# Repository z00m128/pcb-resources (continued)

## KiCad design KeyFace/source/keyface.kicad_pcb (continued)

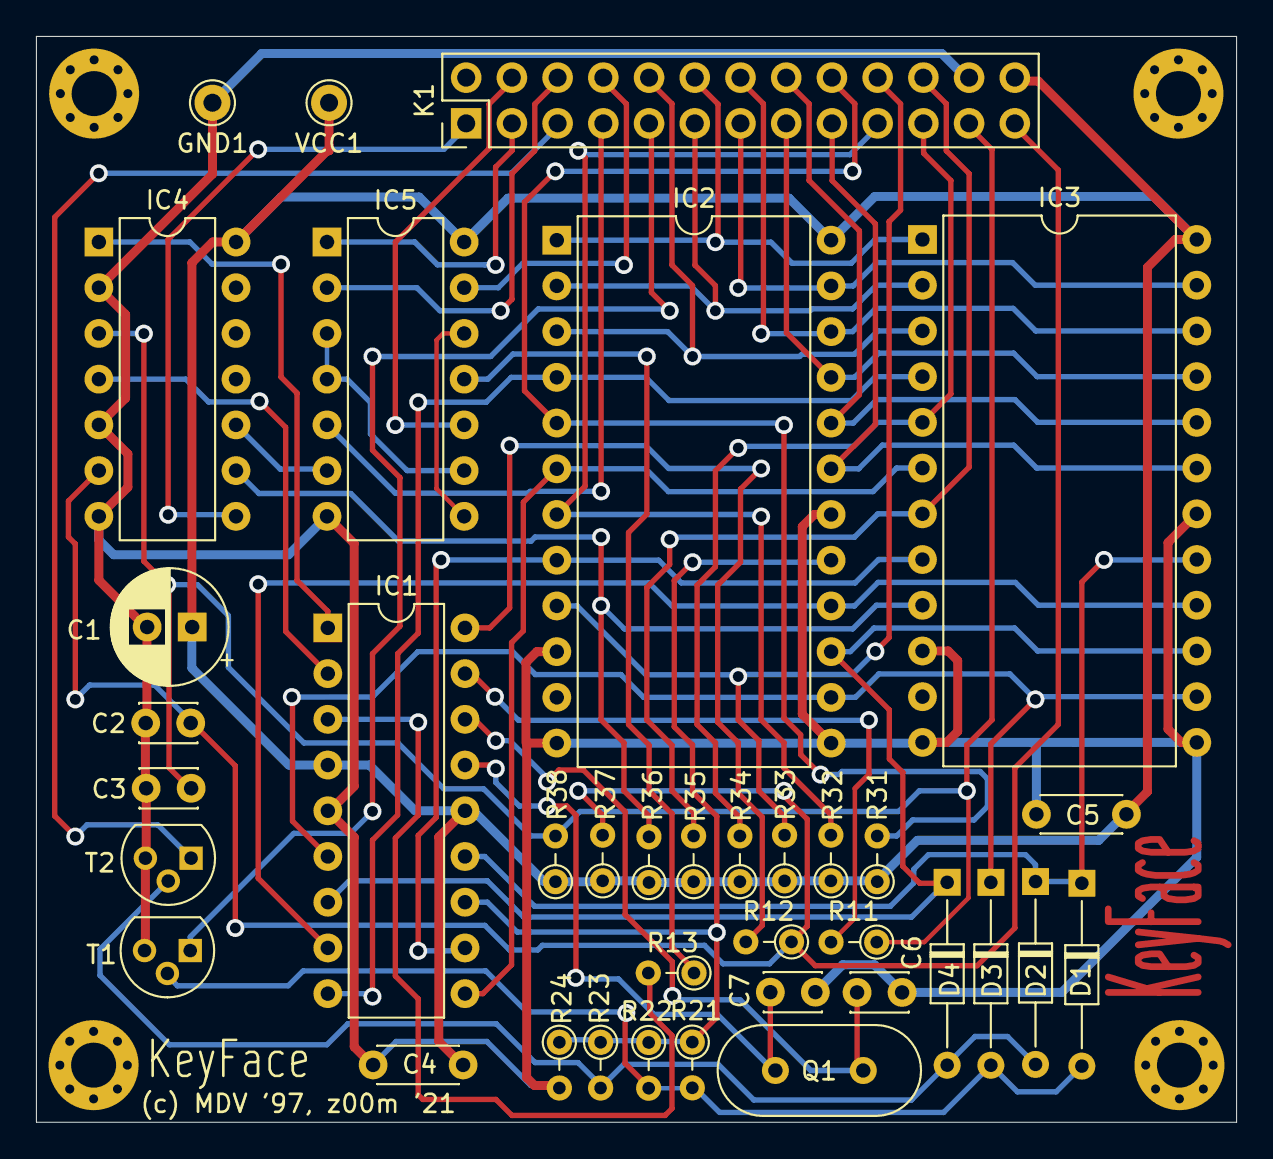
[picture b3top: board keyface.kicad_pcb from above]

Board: 2 copper layers, 66.7 x 60.3 mm, 41 parts (0 on the bottom side), 47 nets.

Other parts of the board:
H1, H2, H3, H4: MountingHole_2.5mm_Pad_Via

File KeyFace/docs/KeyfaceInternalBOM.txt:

C1               1  100uF                 Polarized capacitor, radial, 6.3mm x 2.5mm
C2,C3            2  47p                   Unpolarized capacitor, disc, 3 mm x 2mm x 2.5mm
C4,C5            2  100n                  Unpolarized capacitor, disc, 4.3 mm x 1.9mm x 5mm
C6,C7            2  33p                   Unpolarized capacitor, disc, 3 mm x 2mm x 2.5mm
D1,D2,D3,D4      4  BAT42                 Diode schottky, DO-35
IC1              1  PIC16C56 or PIC16F84  Micro controller, DIP 18
IC2,IC3          2  MHB8804               Analog switching array, DIP 24W
IC4              1  74HCT125              Quad buffer 3-State outputs, DIP 14
IC5              1  74HCT32               Quad 2-input OR, DIP 14
Q1               1  4 MHz                 Two pin crystal, HC49U (H49S), THT
R11,R12,R13      3  560R                  Resistor 0.25W, small, THT
R21,R22,R23,R24  4  10k                   Resistor 0.25W, small, THT
R31,R32,R33,R34  8  4k7                   Resistor 0.25W, small, THT
R35,R36,R37,R38  
T1,T2            1  BC547                 0.1A Ic, 45V Vce, Small Signal NPN Transistor, TO-92
K1               1  Conn_02x13_Odd_Even   Generic connector, double row, 2x13, 2.54 mm raster

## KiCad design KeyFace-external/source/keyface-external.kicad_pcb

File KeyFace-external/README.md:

# KeyFace External for ZX Spectrum
A PS/2 keyboard interface for ZX Spectrum, external version. This PCB was created from scratch, but I tried to mimic component layout as was seen on original PCB from Kompakt Servis. It's verified and working.

## Schematic Diagram

## Populated PCB

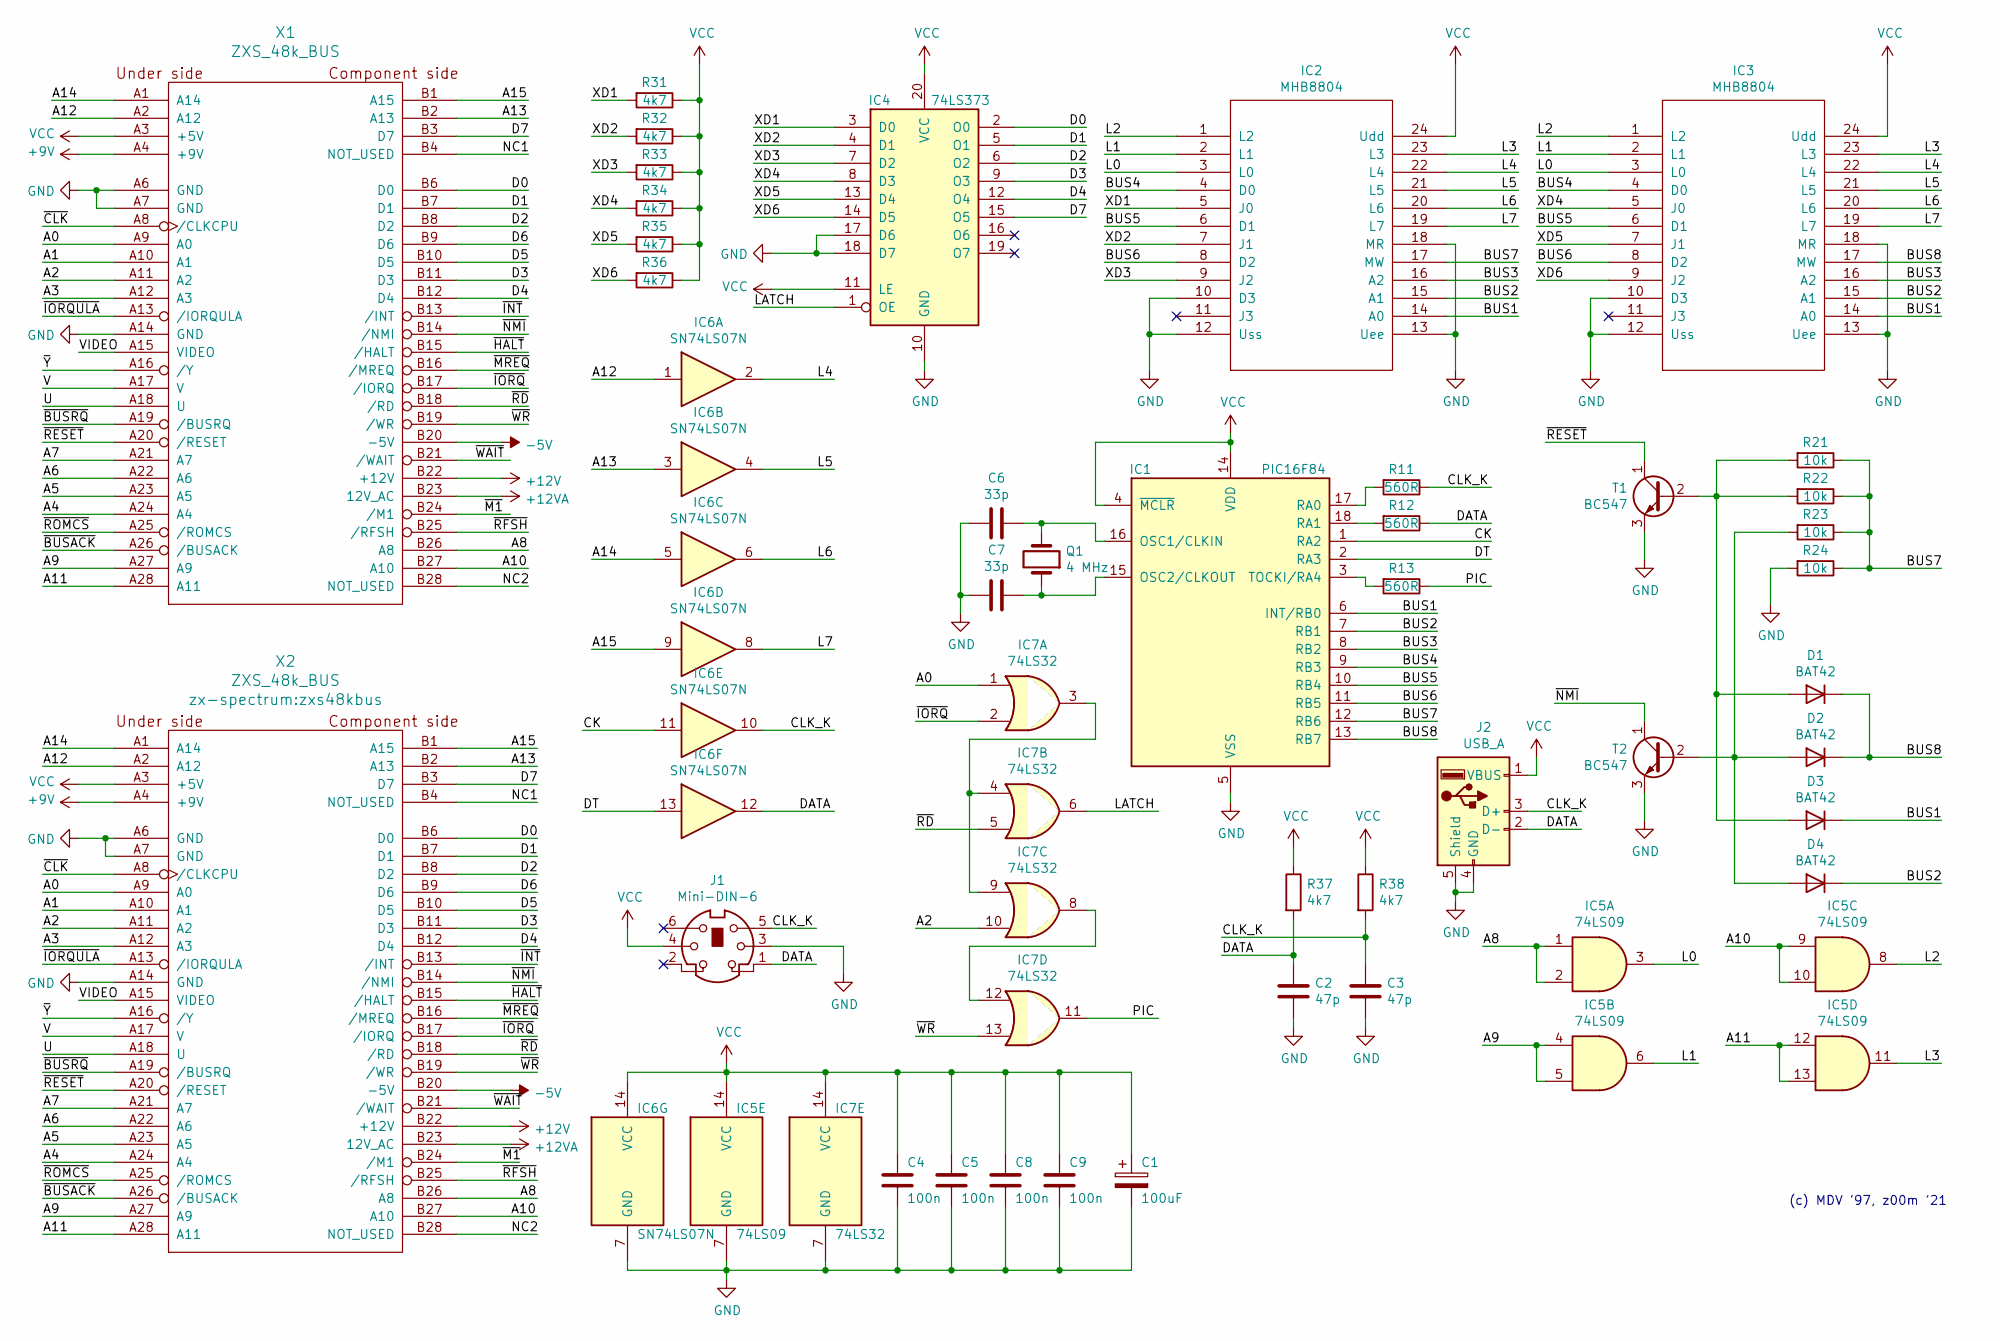
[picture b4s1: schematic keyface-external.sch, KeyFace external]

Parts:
C1: 100uF; CP_Radial_D6.3mm_P2.50mm
C2, C3: 47p; C_Disc_D3.0mm_W2.0mm_P2.50mm
C4, C5, C8, C9: 100n; C_Disc_D4.3mm_W1.9mm_P5.00mm
C6, C7: 33p; C_Disc_D3.0mm_W2.0mm_P2.50mm
D1, D2, D3, D4: BAT42; D_DO-35_SOD27_P7.62mm_Horizontal
IC1: PIC16F84; DIP-18_W7.62mm
IC2, IC3: MHB8804; DIP-24_W15.24mm
IC4: 74LS373; DIP-20_W7.62mm
IC5: 74LS09; DIP-14_W7.62mm
IC6: SN74LS07N; DIP-14_W7.62mm
IC7: 74LS32; DIP-14_W7.62mm
J1: Mini-DIN-6; MiniDin6
J2: USB_A; USB_A_Wuerth_614004134726_Horizontal
Q1: 4 MHz; Crystal_HC49-U_Vertical
R11, R12, R13: 560R; R_Axial_DIN0204_L3.6mm_D1.6mm_P2.54mm_Vertical
R21, R22, R23, R24: 10k; R_Axial_DIN0204_L3.6mm_D1.6mm_P2.54mm_Vertical
R31, R32, R33, R34, R35, R36, R37, R38: 4k7; R_Axial_DIN0204_L3.6mm_D1.6mm_P2.54mm_Vertical
T1, T2: BC547; TO-92
X1, X2: ZXS_48k_BUS; zxs48kbus

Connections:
+9V: X1.A4 (+9V), X2.A4 (+9V)
+12V: X1.B22 (+12V), X2.B22 (+12V)
+12VA: X1.B23 (12V_AC), X2.B23 (12V_AC)
-5V: X1.B20 (-5V), X2.B20 (-5V)
/A0: IC7.1, X1.A9 (A0), X2.A9 (A0)
/A1: X1.A10 (A1), X2.A10 (A1)
/A2: IC7.10, X1.A11 (A2), X2.A11 (A2)
/A3: X1.A12 (A3), X2.A12 (A3)
/A4: X1.A24 (A4), X2.A24 (A4)
/A5: X1.A23 (A5), X2.A23 (A5)
/A6: X1.A22 (A6), X2.A22 (A6)
/A7: X1.A21 (A7), X2.A21 (A7)
/A8: IC5.1, IC5.2, X1.B26 (A8), X2.B26 (A8)
/A9: IC5.4, IC5.5, X1.A27 (A9), X2.A27 (A9)
/A10: IC5.9, IC5.10, X1.B27 (A10), X2.B27 (A10)
/A11: IC5.12, IC5.13, X1.A28 (A11), X2.A28 (A11)
/A12: IC6.1, X1.A2 (A12), X2.A2 (A12)
/A13: IC6.3, X1.B2 (A13), X2.B2 (A13)
/A14: IC6.5, X1.A1 (A14), X2.A1 (A14)
/A15: IC6.9, X1.B1 (A15), X2.B1 (A15)
/BUS1: D3.1 (K), IC1.6 (INT/RB0), IC2.14 (A0), IC3.14 (A0)
/BUS2: D4.1 (K), IC1.7 (RB1), IC2.15 (A1), IC3.15 (A1)
/BUS3: IC1.8 (RB2), IC2.16 (A2), IC3.16 (A2)
/BUS4: IC1.9 (RB3), IC2.4 (D0), IC3.4 (D0)
/BUS5: IC1.10 (RB4), IC2.6 (D1), IC3.6 (D1)
/BUS6: IC1.11 (RB5), IC2.8 (D2), IC3.8 (D2)
/BUS7: IC1.12 (RB6), IC2.17 (MW), R21.1, R22.1, R23.1, R24.1
/BUS8: D1.1 (K), D2.1 (K), IC1.13 (RB7), IC3.17 (MW)
/CK: IC1.1 (RA2), IC6.11
/CLK_K: C3.1, IC6.10, J1.5, J2.3 (D+), R11.1, R38.2
/D0: IC4.2 (O0), X1.B6 (D0), X2.B6 (D0)
/D1: IC4.5 (O1), X1.B7 (D1), X2.B7 (D1)
/D2: IC4.6 (O2), X1.B8 (D2), X2.B8 (D2)
/D3: IC4.9 (O3), X1.B11 (D3), X2.B11 (D3)
/D4: IC4.12 (O4), X1.B12 (D4), X2.B12 (D4)
/D5: X1.B10 (D5), X2.B10 (D5)
/D6: X1.B9 (D6), X2.B9 (D6)
/D7: IC4.15 (O5), X1.B3 (D7), X2.B3 (D7)
/DATA: C2.1, IC6.12, J1.1, J2.2 (D-), R12.1, R37.2
/DT: IC1.2 (RA3), IC6.13
/L0: IC2.3 (L0), IC3.3 (L0), IC5.3
/L1: IC2.2 (L1), IC3.2 (L1), IC5.6
/L2: IC2.1 (L2), IC3.1 (L2), IC5.8
/L3: IC2.23 (L3), IC3.23 (L3), IC5.11
/L4: IC2.22 (L4), IC3.22 (L4), IC6.2
/L5: IC2.21 (L5), IC3.21 (L5), IC6.4
/L6: IC2.20 (L6), IC3.20 (L6), IC6.6
/L7: IC2.19 (L7), IC3.19 (L7), IC6.8
/LATCH: IC4.1 (OE), IC7.6
/NC1: X1.B4 (NOT_USED), X2.B4 (NOT_USED)
/NC2: X1.B28 (NOT_USED), X2.B28 (NOT_USED)
/PIC: IC7.11, R13.1
/U: X1.A18 (U), X2.A18 (U)
/V: X1.A17 (V), X2.A17 (V)
/VIDEO: X1.A15 (VIDEO), X2.A15 (VIDEO)
/XD1: IC2.5 (J0), IC4.3 (D0), R31.2
/XD2: IC2.7 (J1), IC4.4 (D1), R32.2
/XD3: IC2.9 (J2), IC4.7 (D2), R33.2
/XD4: IC3.5 (J0), IC4.8 (D3), R34.2
/XD5: IC3.7 (J1), IC4.13 (D4), R35.2
/XD6: IC3.9 (J2), IC4.14 (D5), R36.2
/~BUSACK: X1.A26 (/BUSACK), X2.A26 (/BUSACK)
/~BUSRQ: X1.A19 (/BUSRQ), X2.A19 (/BUSRQ)
/~CLK: X1.A8 (/CLKCPU), X2.A8 (/CLKCPU)
/~HALT: X1.B15 (/HALT), X2.B15 (/HALT)
/~INT: X1.B13 (/INT), X2.B13 (/INT)
/~IORQ: IC7.2, X1.B17 (/IORQ), X2.B17 (/IORQ)
/~IORQULA: X1.A13 (/IORQULA), X2.A13 (/IORQULA)
/~M1: X1.B24 (/M1), X2.B24 (/M1)
/~MREQ: X1.B16 (/MREQ), X2.B16 (/MREQ)
/~NMI: T2.1 (C), X1.B14 (/NMI), X2.B14 (/NMI)
/~RD: IC7.5, X1.B18 (/RD), X2.B18 (/RD)
/~RESET: T1.1 (C), X1.A20 (/RESET), X2.A20 (/RESET)
/~RFSH: X1.B25 (/RFSH), X2.B25 (/RFSH)
/~ROMCS: X1.A25 (/ROMCS), X2.A25 (/ROMCS)
/~WAIT: X1.B21 (/WAIT), X2.B21 (/WAIT)
/~WR: IC7.13, X1.B19 (/WR), X2.B19 (/WR)
/~Y: X1.A16 (/Y), X2.A16 (/Y)
GND: C1.2, C2.2, C3.2, C4.2, C5.2, C6.2, C7.2, C8.2, C9.2, IC1.5 (VSS), IC2.10 (D3), IC2.12 (Uss), IC2.13 (Uee), IC2.18 (MR), IC3.10 (D3), IC3.12 (Uss), IC3.13 (Uee), IC3.18 (MR), IC4.10 (GND), IC4.17 (D6), IC4.18 (D7), IC5.7 (GND), IC6.7 (GND), IC7.7 (GND), J1.3, J2.4 (GND), J2.5 (Shield), R24.2, T1.3 (E), T2.3 (E), X1.A6 (GND), X1.A7 (GND), X1.A14 (GND), X2.A6 (GND), X2.A7 (GND), X2.A14 (GND)
unnamed: C6.1, IC1.16 (OSC1/CLKIN), Q1.2
unnamed: C7.1, IC1.15 (OSC2/CLKOUT), Q1.1
unnamed: D1.2 (A), D3.2 (A), R21.2, R22.2, T1.2 (B)
unnamed: D2.2 (A), D4.2 (A), R23.2, T2.2 (B)
unnamed: IC1.3 (TOCKI/RA4), R13.2
unnamed: IC1.17 (RA0), R11.2
unnamed: IC1.18 (RA1), R12.2
unnamed: IC7.3, IC7.4, IC7.9
unnamed: IC7.8, IC7.12
VCC: C1.1, C4.1, C5.1, C8.1, C9.1, IC1.4 (~MCLR~), IC1.14 (VDD), IC2.24 (Udd), IC3.24 (Udd), IC4.11 (LE), IC4.20 (VCC), IC5.14 (VCC), IC6.14 (VCC), IC7.14 (VCC), J1.4, J2.1 (VBUS), R31.1, R32.1, R33.1, R34.1, R35.1, R36.1, R37.1, R38.1, X1.A3 (+5V), X2.A3 (+5V)

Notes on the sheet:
(c) MDV '97, z00m '21

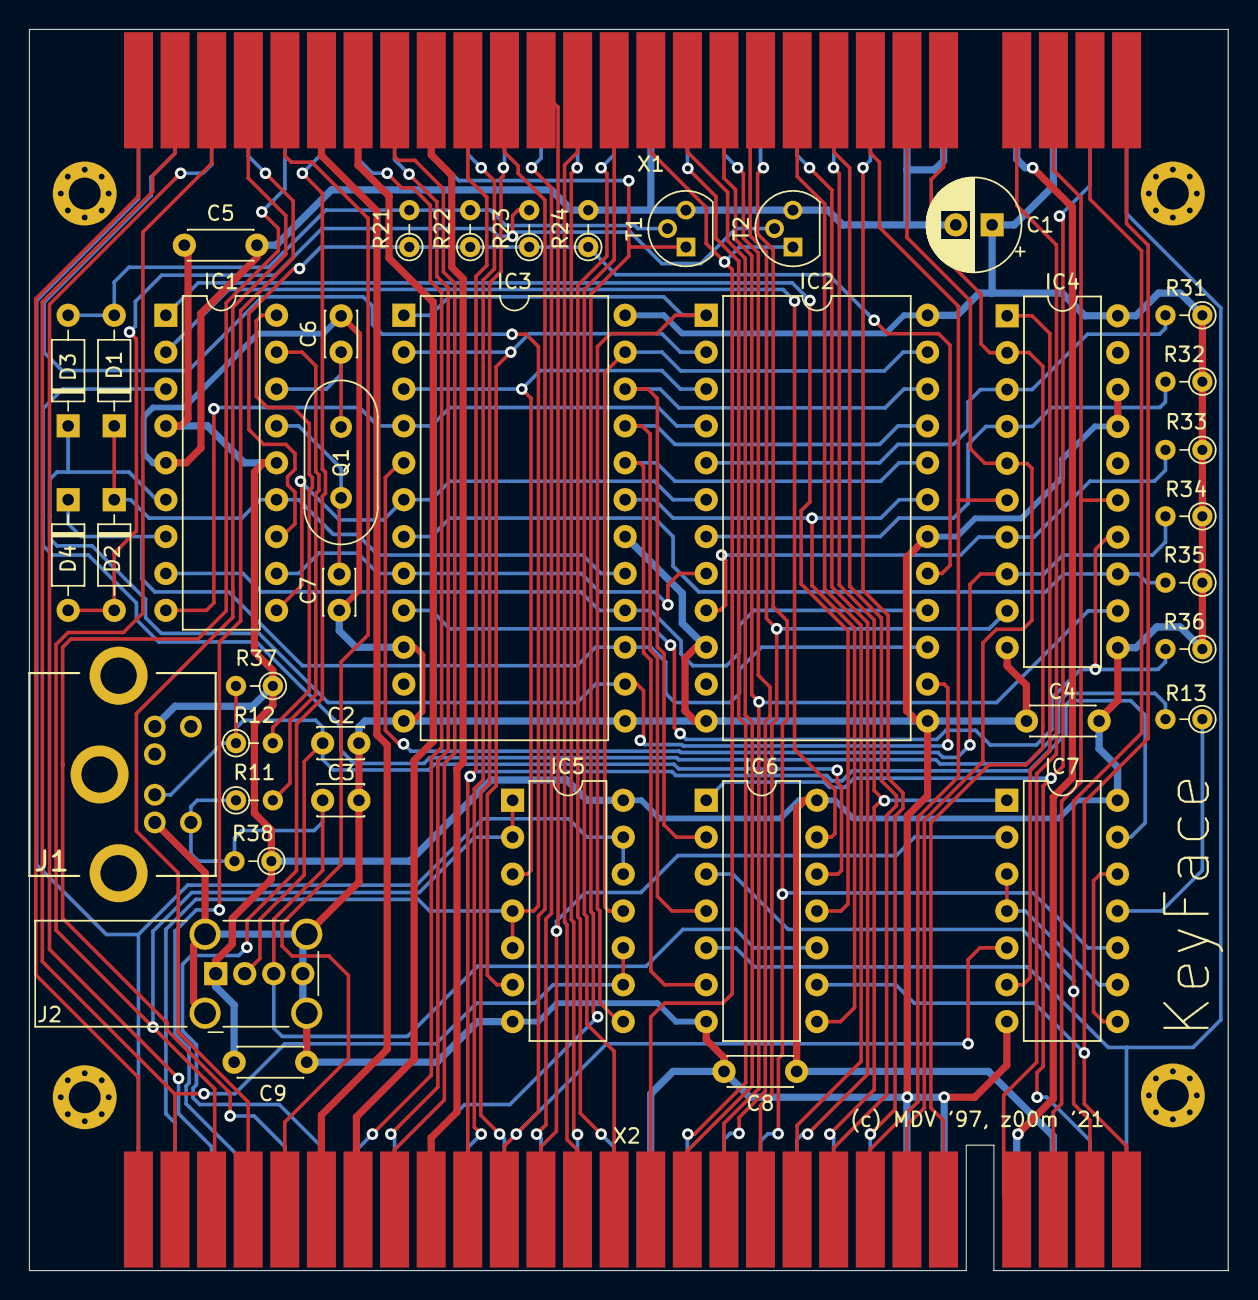
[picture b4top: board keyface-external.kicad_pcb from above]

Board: 2 copper layers, 82.6 x 85.5 mm, 46 parts (0 on the bottom side), 89 nets.

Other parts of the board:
H1, H2, H3, H4: MountingHole_2.2mm_M2_Pad_Via

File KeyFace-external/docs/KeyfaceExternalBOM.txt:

C1               1  100uF                 Polarized capacitor, radial, 6.3mm x 2.5mm
C2,C3            2  47p                   Unpolarized capacitor, disc, 3 mm x 2mm x 2.5mm
C4,C5,C8,C9      4  100n                  Unpolarized capacitor, disc, 4.3 mm x 1.9mm x 5mm
C6,C7            2  33p                   Unpolarized capacitor, disc, 3 mm x 2mm x 2.5mm
D1,D2,D3,D4      4  BAT42                 Diode schottky, DO-35
IC1              1  PIC16C56 or PIC16F84  Micro controller, DIP 18
IC2,IC3          2  MHB8804               Analog switching array, DIP 24W
IC4              1  74HCT373              8-bit Latch, 3-state outputs, DIP 20
IC5              1  74LS09                Quad 2-Input AND Gates with Open-Collector Outputs, DIP 14
IC6              1  74LS07                Hex Buffers and Drivers With Open Collector High Voltage Outputs, DIP 14
IC7              1  74HCT32               Quad 2-input OR, DIP 14
Q1               1  4 MHz                 Two pin crystal, HC49U (H49S), THT
R11,R12,R13      3  560R                  Resistor 0.25W, small, THT
R21,R22,R23,R24  4  10k                   Resistor 0.25W, small, THT
R31,R32,R33,R34  8  4k7                   Resistor 0.25W, small, THT
R35,R36,R37,R38
T1,T2            1  BC547                 0.1A Ic, 45V Vce, Small Signal NPN Transistor, TO-92
X1               1  ZXS_48k_BUS           WK 465 80
J1               1  Mini-DIN-6            mini DIN, female, 6 pin, angled 90deg, THT
J2               1  USB_A                 USB A, socket, angled 90deg, side, THT

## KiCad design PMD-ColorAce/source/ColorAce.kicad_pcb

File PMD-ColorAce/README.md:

# ColorAce for PMD85

My own iteration of PCB for ColorAce enhancement for PMD85 computer. PCB is not verified.

## 3D render

## Detailed information
Complete informations in slovak language: [External link](https://pmd85.borik.net/wiki/ColorAce)

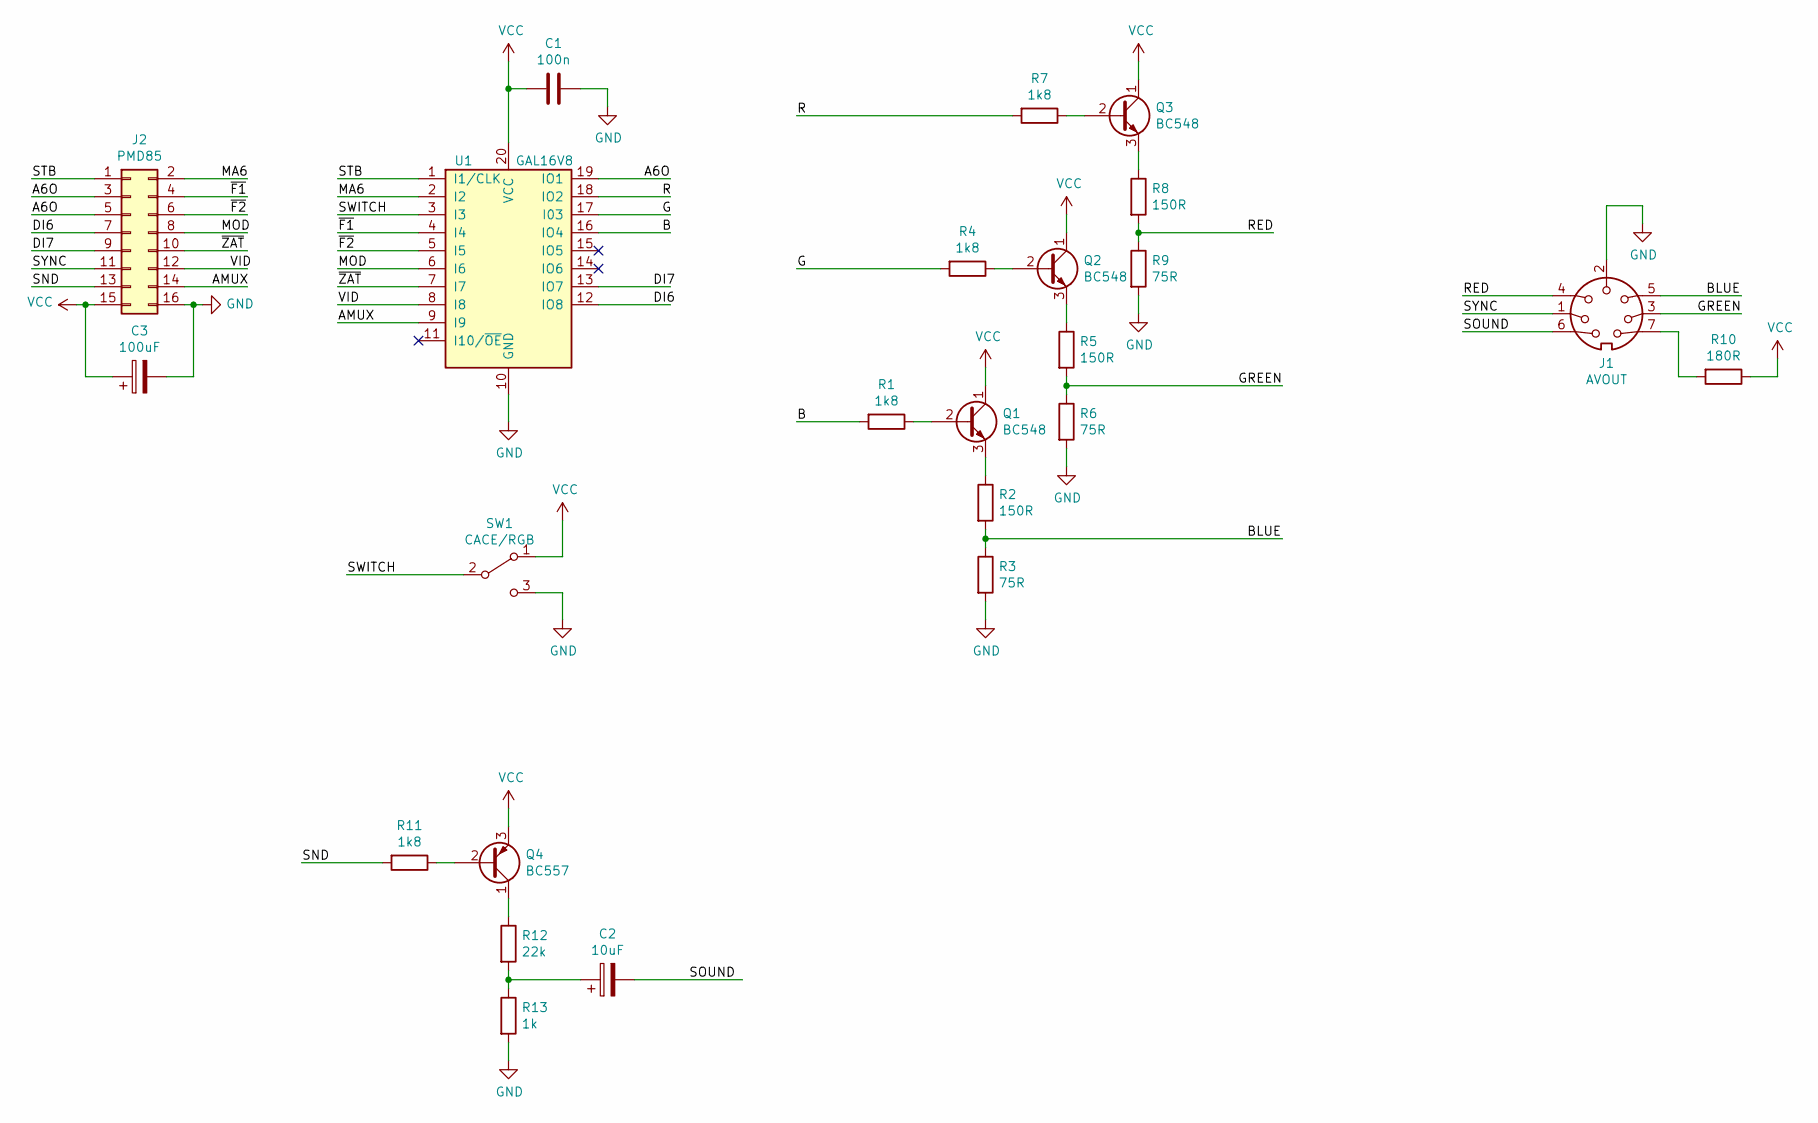
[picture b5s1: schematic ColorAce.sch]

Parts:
C1: 100n; C_Disc_D7.0mm_W2.5mm_P5.00mm
C2: 10uF; CP_Radial_D6.3mm_P2.50mm
C3: 100uF; CP_Radial_D6.3mm_P2.50mm
J1: AVOUT; PinHeader_1x07_P2.54mm_Horizontal
J2: PMD85; PinHeader_2x08_P2.54mm_Vertical
Q1, Q2, Q3: BC548; TO-92_Inline
Q4: BC557; TO-92_Inline
R1, R4, R7, R11: 1k8; R_Axial_DIN0207_L6.3mm_D2.5mm_P7.62mm_Horizontal
R2, R5, R8: 150R; R_Axial_DIN0207_L6.3mm_D2.5mm_P7.62mm_Horizontal
R3, R6, R9: 75R; R_Axial_DIN0207_L6.3mm_D2.5mm_P7.62mm_Horizontal
R10: 180R; R_Axial_DIN0207_L6.3mm_D2.5mm_P7.62mm_Horizontal
R12: 22k; R_Axial_DIN0207_L6.3mm_D2.5mm_P7.62mm_Horizontal
R13: 1k; R_Axial_DIN0207_L6.3mm_D2.5mm_P7.62mm_Horizontal
SW1: CACE/RGB; PinHeader_1x03_P2.54mm_Horizontal
U1: GAL16V8; DIP-20_W7.62mm_LongPads

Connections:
/A6O: J2.3, J2.5, U1.19 (IO1)
/AMUX: J2.14, U1.9 (I9)
/B: R1.2, U1.16 (IO4)
/BLUE: J1.5, R2.2, R3.1
/DI6: J2.7, U1.12 (IO8)
/DI7: J2.9, U1.13 (IO7)
/G: R4.2, U1.17 (I03)
/GREEN: J1.3, R5.2, R6.1
/MA6: J2.2, U1.2 (I2)
/MOD: J2.8, U1.6 (I6)
/R: R7.2, U1.18 (IO2)
/RED: J1.4, R8.2, R9.1
/SND: J2.13, R11.2
/SOUND: C2.2, J1.6
/STB: J2.1, U1.1 (I1/CLK)
/SWITCH: SW1.2 (B), U1.3 (I3)
/SYNC: J1.1, J2.11
/VID: J2.12, U1.8 (I8)
/~F1: J2.4, U1.4 (I4)
/~F2: J2.6, U1.5 (I5)
/~ZAT: J2.10, U1.7 (I7)
GND: C1.1, C3.2, J1.2, J2.16, R3.2, R6.2, R9.2, R13.2, SW1.3 (C), U1.10 (GND); also elsewhere on the board
unnamed: C2.1, R12.2, R13.1
unnamed: J1.7, R10.2
unnamed: Q1.2 (B), R1.1
unnamed: Q1.3 (E), R2.1
unnamed: Q2.2 (B), R4.1
unnamed: Q2.3 (E), R5.1
unnamed: Q3.2 (B), R7.1
unnamed: Q3.3 (E), R8.1
unnamed: Q4.1 (C), R12.1
unnamed: Q4.2 (B), R11.1
VCC: C1.2, C3.1, J2.15, Q1.1 (C), Q2.1 (C), Q3.1 (C), Q4.3 (E), R10.1, SW1.1 (A), U1.20 (VCC)

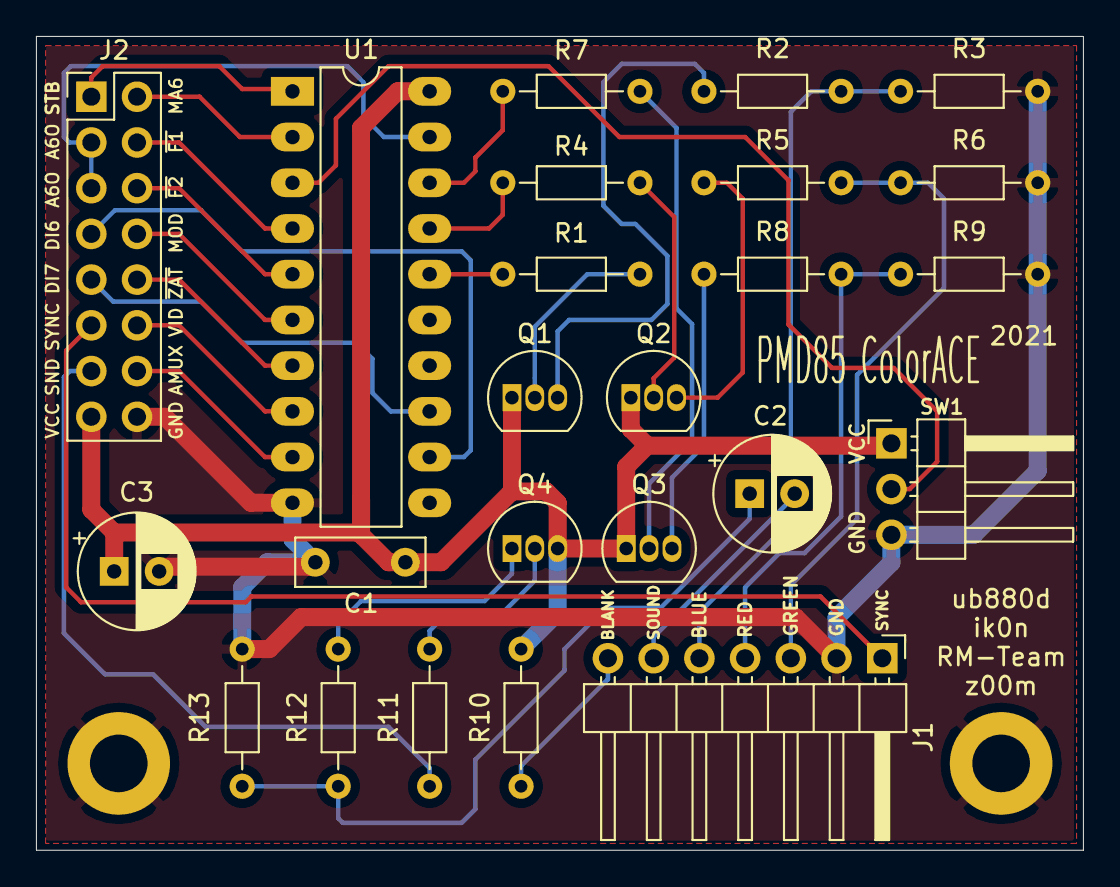
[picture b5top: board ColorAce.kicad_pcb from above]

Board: 2 copper layers, 58.2 x 45.2 mm, 26 parts (0 on the bottom side), 33 nets.

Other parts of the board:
MH1, MH2: MountingHole_3.2mm_M3_ISO7380_Pad

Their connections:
GND: MH1.1, MH2.1; also elsewhere on the board

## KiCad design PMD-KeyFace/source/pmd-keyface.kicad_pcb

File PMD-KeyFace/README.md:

# KeyFace for PMD85

My own iteration of PS/2 keyboard interface for PMD85. The PCB is not verified.

## 3D render

## Detailed informations
Complete informations in slovak language: [External link](https://pmd85.borik.net/wiki/Blog:Keyface)

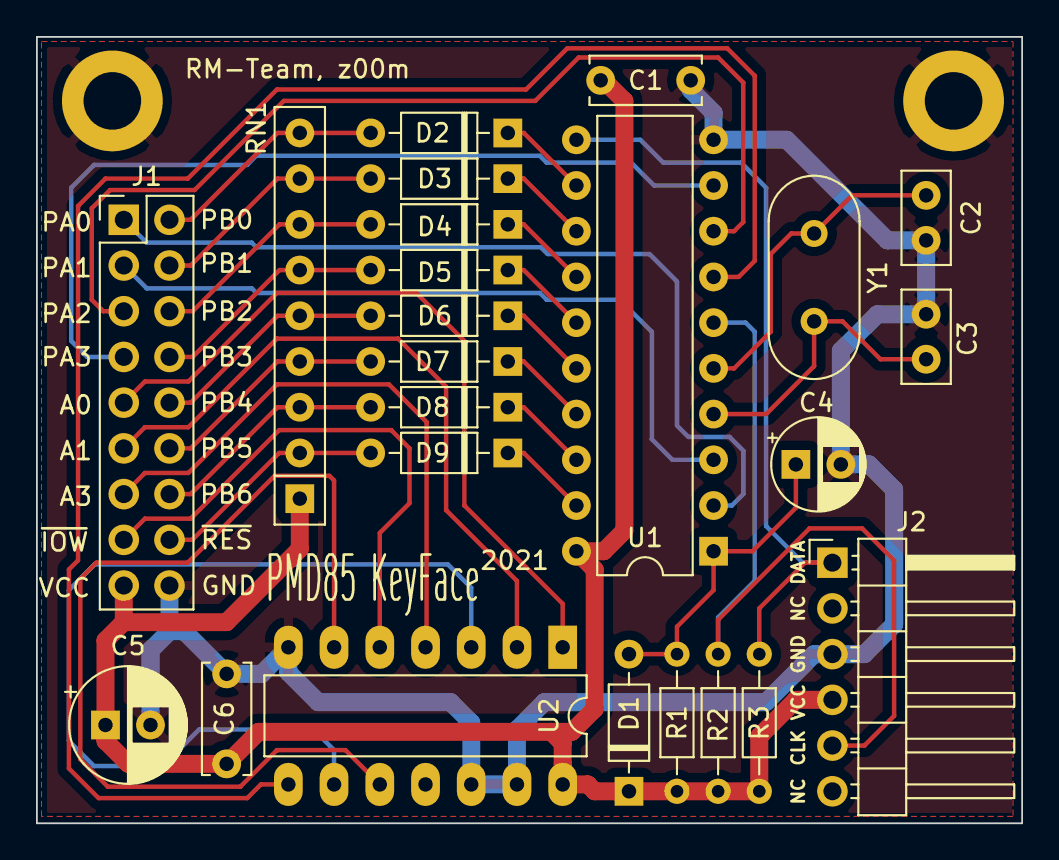
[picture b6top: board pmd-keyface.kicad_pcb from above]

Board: 2 copper layers, 54.7 x 43.7 mm, 26 parts (0 on the bottom side), 34 nets.

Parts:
C1, C6: 100n; C_Disc_D6.0mm_W2.5mm_P5.00mm
C2, C3: 18p; C_Disc_D5.0mm_W2.5mm_P2.50mm
C4: 1uF; CP_Radial_D5.0mm_P2.50mm
C5: 100uF; CP_Radial_D6.3mm_P2.50mm
D1, D2, D3, D4, D5, D6, D7, D8, D9: 1N4148; D_DO-35_SOD27_P7.62mm_Horizontal
J1: PMD85; PinHeader_2x09_P2.54mm_Vertical
J2: Mini-DIN-6; PinHeader_1x06_P2.54mm_Horizontal
MH1, MH2: MountingHole_3.2mm_M3_DIN965_Pad
R1: 10k; R_Axial_DIN0204_L3.6mm_D1.6mm_P7.62mm_Horizontal
R2, R3: 1k; R_Axial_DIN0204_L3.6mm_D1.6mm_P7.62mm_Horizontal
RN1: 47k; R_Array_SIP9
U1: ATtiny2313-20PU; DIP-20_W7.62mm
U2: 74LS32; DIP-14_W7.62mm_LongPads
Y1: 20MHz; Crystal_HC49-U_Vertical

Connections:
/0F4h: U1.7, U2.8
/A0: J1.9, U2.1
/A1: J1.11, U2.2
/A3: J1.13, U2.4
/CLK: J2.5, R2.2, U1.6
/DATA: J2.1, R3.2, U1.11
/PA0: J1.1, U1.2
/PA1: J1.3, U1.3
/PA2: J1.5, U1.8
/PA3: J1.7, U1.9
/PB0: D2.2, J1.2, RN1.9
/PB1: D3.2, J1.4, RN1.8
/PB2: D4.2, J1.6, RN1.7
/PB3: D5.2, J1.8, RN1.6
/PB4: D6.2, J1.10, RN1.5
/PB5: D7.2, J1.12, RN1.4
/PB6: D8.2, J1.14, RN1.3
/RESET: D9.1, U1.19
/ROW0: D2.1, U1.12
/ROW1: D3.1, U1.13
/ROW2: D4.1, U1.14
/ROW3: D5.1, U1.15
/ROW4: D6.1, U1.16
/SHIFT: D7.1, U1.17
/STOP: D8.1, U1.18
/~IOW: J1.15, U2.5
/~RES: D9.2, J1.16, RN1.2
GND: C1.1, C2.2, C3.2, C4.2, C5.2, C6.2, J1.18, J2.3, MH1.1, MH2.1, U1.10, U2.7, U2.12, U2.13
unnamed: C2.1, U1.5, Y1.1
unnamed: C3.1, U1.4, Y1.2
unnamed: C4.1, D1.2, R1.2, U1.1
unnamed: U2.3, U2.9
unnamed: U2.6, U2.10
VCC: C1.2, C5.1, C6.1, D1.1, J1.17, J2.4, R1.1, R2.1, R3.1, RN1.1, U1.20, U2.14

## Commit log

2025-03-27 README.md updated.
2025-03-27 Didaktik M92 added.
2025-03-27 Didaktik Kompakt, version 2.3 added.
2025-03-27 LICENSE.md added.
2025-03-27 README.md updated
    Added link to license.
2025-03-27 Lamac CPM board added.
2025-03-27 LICENSE.md updated.
2025-03-27 README.md created.
2025-03-27 README.md created
2025-03-27 PMD Keyface and ColorAce added.
2025-03-27 Fixed external ColorAce link.
2025-03-28 KeyFace added.
2025-03-28 Melodik2 added.
2025-03-28 Fixed Melodik2 rev1.0 screenshot, added Melodik2 rev2.0 schematic diagram.
2025-03-28 Custom libraries for KiCad added.
2025-03-28 Minor fixes on Didaktik Kompakt board.
2025-04-02 Cosmetic change on DM92 board.
2025-04-02 ZX Cherry KB preview added.
2025-04-02 Added Toastrack replica preview.
2025-04-26 ZX-Cherry-KB: KiCad project added.
2025-04-29 ZX-Cherry-KB: fixed placement of holes.
2025-04-29 ZX-Cherry-KB: added fabrication files, screenshots updated.
2025-04-29 ZX-Cherry-KB: updated Readme.md.
2025-04-29 ZX-Cherry-KB: Added prototype pics.
2025-04-29 Updated Readme.md.
2025-04-29 ZX-Cherry-KB: added BOM.
2025-04-29 ZX-Cherry-KB: added layout SVG.
2025-04-29 Toastrack: Added board resources and pics.
2025-04-29 Toastrack: added BOM and fixed README.md
2025-05-01 Toastrack: fixed xray screenshot.
2025-09-18 ZX-Cherry-KB: fixed fabrication files and added zip file.
